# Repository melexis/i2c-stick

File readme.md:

# Melexis i2c-stick

Current version: V1.6.0

The web interface here:  
https://www.melexis.com/i2c-stick/

The i2c-stick:  
[web_interface/i2c-stick.md](web_interface/i2c-stick.md)

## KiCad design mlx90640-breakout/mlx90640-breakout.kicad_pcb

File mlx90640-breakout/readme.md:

# MLX90640-41 Breakout

## The sensor

Breakout PBC for MLX90640 & MLX90641:  
https://melexis.com/mlx90640  
https://melexis.com/mlx90641

Order codes for the sensor:

### MLX90640:  

32x24 pixel thermal camera

- MLX90640ESF-BAB-000-SP: Small FoV (55x35)
- MLX90640ESF-BAA-000-SP: Wide FoV (110x75)

### MLX90641:

16x12 pixel thermal camera

- MLX90641ESF-BCA-000-SP: Small FoV (55x35)
- MLX90641ESF-BCB-000-SP: Wide FoV (110x75)

Or contact our sales team at: https://www.melexis.com/en/contact/sales-contact

Where to buy? https://www.melexis.com/en/contact/distributors

## Get started

This board works together with any 3.3V I2C master.  
Have a look at our `I2C STICK` for evaluation pursposes.  
The board uses the QWIIC connector system for I2C & Supply.

QWIIC: https://www.sparkfun.com/qwiic

## The board

### Schema

### Layout

### 3D View

### 3D Model

[mlx90640-breakout.step](output/mlx90640-breakout.step)  

### Images

todo

### Optional socket:

Mill-Max Manufacturing Corp. - 917-43-208-41-005000  
  
https://www.digikey.com/en/products/detail/mill-max-manufacturing-corp/917-43-208-41-005000/1212173   
Note: 4 pins would have to be cut in order to fit the foot print.

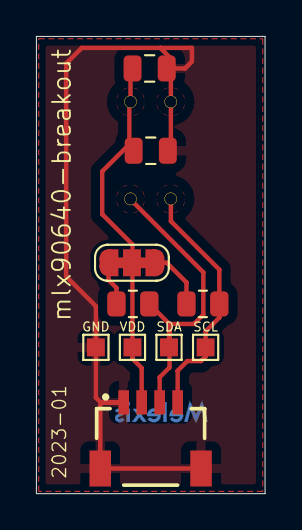
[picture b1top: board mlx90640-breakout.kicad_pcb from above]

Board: 2 copper layers, 12.7 x 25.4 mm, 11 parts (1 on the bottom side), 6 nets.

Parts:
C1: 100n; C_0805_2012Metric
C2: 10u; C_0805_2012Metric
GND: TestPoint; TestPoint_Pad_1.0x1.0mm
J1: Conn_01x04_Male; QWIIC_STEMMA_QT
JP1: SolderJumper_3_Bridged123; SolderJumper-3_P1.3mm_Bridged12_RoundedPad1.0x1.5mm_NumberL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
R1, R2: 4K7; R_0805_2012Metric
SCL: TestPoint; TestPoint_Pad_1.0x1.0mm
SDA: TestPoint; TestPoint_Pad_1.0x1.0mm
U1: MLX90640; mlx90640_41
VDD: TestPoint; TestPoint_Pad_1.0x1.0mm

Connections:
/GND: C1.2, C2.2, GND.1, J1.1, J1.NC1, J1.NC2, U1.3 (GND)
/SCL: J1.4, R1.2, SCL.1, U1.4 (SCL)
/SDA: J1.3, R2.2, SDA.1, U1.1 (SDA)
/VDD: C1.1, C2.1, J1.2, JP1.2 (C), U1.2 (VDD), VDD.1
unnamed: JP1.1 (A), R2.1
unnamed: JP1.3 (B), R1.1

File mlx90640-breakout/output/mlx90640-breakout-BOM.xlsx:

Item | Qty | Reference(s) | Value | LibPart | Footprint | Datasheet
1 | 1 | C1 | 100n | pspice:C | Capacitor_SMD:C_0805_2012Metric | ~
2 | 1 | C2 | 10u | pspice:C | Capacitor_SMD:C_0805_2012Metric | ~
3 | 1 | J1 | Conn_01x04_Male | Connector:Conn_01x04_Male | melexis-temperature:QWIIC_STEMMA_QT | https://www.sparkfun.com/products/14417
5 | 2 | R1, R2 | 4K7 | Device:R | Resistor_SMD:R_0805_2012Metric | ~
7 | 1 | U1 | MLX90640 | melexis-temperature:MLX90640 | melexis-temperature:mlx90640_41 | https://melexis.com/mlx90640
 |  |  | Alt #1 | MLX90640ESF-BAA-000-TU | 32x24 pixel, wide field of view
 |  |  | Alt #2 | MLX90640ESF-BAB-000-TU | 32x24 pixel, small field of view
 |  |  | Alt #3 | MLX90641ESF-BCA-000-TU | 16x12 pixel, wide field of view
 |  |  | Alt #4 | MLX90641ESF-BCB-000-TU | 16x12 pixel, small field of view

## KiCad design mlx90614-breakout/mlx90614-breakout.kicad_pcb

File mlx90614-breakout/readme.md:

# MLX90614 Breakout

## The sensor

Breakout PBC for MLX90614:  
https://melexis.com/mlx90614

Order codes for the sensor:

### Standard accuracy:  

- MLX90614ESF-BAA-000-SP: 90 Deg FoV
- MLX90614ESF-BCC-000-SP: 35 Deg FoV
- MLX90614ESF-BCF-000-SP: 10 Deg FoV
- MLX90614ESF-BCI-000-SP:  5 Deg FoV

### Medical Accuracy:

- MLX90614ESF-DCC-000-SP: 35 Deg FoV
- MLX90614ESF-DCI-000-SP:  5 Deg FoV

Contact our sales team at: https://www.melexis.com/en/contact/sales-contact

Where to buy? https://www.melexis.com/en/contact/distributors

## Get started

This board works together with any 3.3V I2C master.  
Have a look at our `I2C STICK` for evaluation pursposes.  
The board uses the QWIIC connector system for I2C & Supply.

QWIIC: https://www.sparkfun.com/qwiic

## The board

### Schema

### Layout

### 3D View

### 3D Model

[mlx90614-breakout.step](output/mlx90614-breakout.step)  

### Images

todo

### Optional socket:

Mill-Max Manufacturing Corp. - 917-43-104-41-005000  
  
https://www.digikey.com/en/products/detail/mill-max-manufacturing-corp/917-43-104-41-005000/1212171

### Optional spacer:

PCB to sensor spacer:  
https://www.digikey.com/en/products/detail/bivar-inc/514-070/3096249  
https://www.digikey.com/en/products/detail/assmann-wsw-components/V4555/3511514

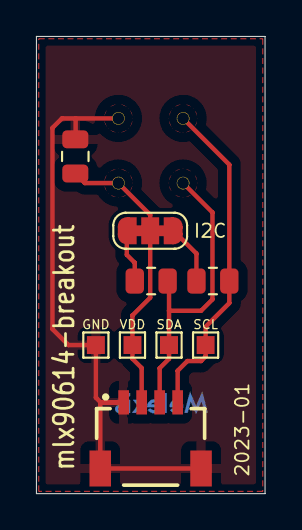
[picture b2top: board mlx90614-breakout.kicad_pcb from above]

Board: 2 copper layers, 12.7 x 25.4 mm, 10 parts (1 on the bottom side), 6 nets.

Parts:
C1: 100n; C_0805_2012Metric
GND: TestPoint; TestPoint_Pad_1.0x1.0mm
I2C: SolderJumper_3_Bridged123; SolderJumper-3_P1.3mm_Bridged12_RoundedPad1.0x1.5mm_NumberL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
J1: Conn_01x04_Male; QWIIC_STEMMA_QT
R1, R2: 4K7; R_0805_2012Metric
SCL: TestPoint; TestPoint_Pad_1.0x1.0mm
SDA: TestPoint; TestPoint_Pad_1.0x1.0mm
U1: MLX90614; mlx90614
VDD: TestPoint; TestPoint_Pad_1.0x1.0mm

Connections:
/GND: C1.2, GND.1, J1.1, J1.NC1, J1.NC2, U1.4 (VSS)
/SCL: J1.4, R1.2, SCL.1, U1.1 (SCL/VZ)
/SDA: J1.3, R2.2, SDA.1, U1.2 (SDA/PWM)
/VDD: C1.1, I2C.2 (C), J1.2, U1.3 (VDD), VDD.1
unnamed: I2C.1 (A), R2.1
unnamed: I2C.3 (B), R1.1

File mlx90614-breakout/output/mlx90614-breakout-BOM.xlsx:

Item | Qty | Reference(s) | Value | LibPart | Footprint | Datasheet | MANUFACTURER
1 | 1 | C1 | 100n | 90632_speculum_flex-rescue:C-pspice | Capacitor_SMD:C_0805_2012Metric
2 | 1 | J1 | Conn_01x04_Male | Connector:Conn_01x04_Male | melexis-temperature:QWIIC_STEMMA_QT | ~ | https://www.sparkfun.com/products/14417
4 | 2 | R1, R2 | 4K7 | Device:R | Resistor_SMD:R_0805_2012Metric | ~
6 | 1 | U1 | MLX90614 | melexis-temperature:MLX90614 | melexis-temperature:mlx90614 | https://melexis.com/mlx90614 | Melexis
 |  |  | Alt #1 | MLX90614ESF-DAA-000-TU | 3V, Medical accuracy, FoV 90, up to 180DegC
 |  |  | Alt #2 | MLX90614ESF-DCC-000-TU | 3V, Medical accuracy, FoV 35, up to 180DegC
 |  |  | Alt #3 | MLX90614ESF-DCI-000-TU | 3V, Medical accuracy, FoV 5, up to 180DegC
 |  |  | Alt #4 | MLX90614ESF-BAA-000-TU | 3V, Standard accuracy, FoV 90, up to 380DegC
 |  |  | Alt #5 | MLX90614ESF-BCC-000-TU | 3V, Standard accuracy, FoV 35, up to 380DegC
 |  |  | Alt #6 | MLX90614ESF-BCI-000-TU | 3V, Standard accuracy, FoV 5, up to 380DegC
 |  | U1-Spacer | optional #1 | white, small spacer |  |  | https://www.digikey.com/en/products/detail/bivar-inc/514-070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
 |  |  | optional #2 | red, larger spacer |  |  | https://www.digikey.com/en/products/detail/assmann-wsw-compo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

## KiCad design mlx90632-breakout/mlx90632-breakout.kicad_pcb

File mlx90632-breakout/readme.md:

# MLX90632 Breakout

## The sensor

Breakout PBC for MLX90632:  
https://melexis.com/mlx90632

Order codes for the sensor:

### Standard accuracy:  

- MLX90632SLD-BCB-000-RE: VDD=3.3V & 3.3V I2C levels

### Medical Accuracy:

- MLX90632SLD-DCB-000-RE: VDD=3.3V & 3.3V I2C levels
- MLX90632SLD-DCB-100-RE: VDD=3.3V & 1.8V I2C levels

Or contact our sales team at: https://www.melexis.com/en/contact/sales-contact

Where to buy? https://www.melexis.com/en/contact/distributors

## Get started

This board works together with any 3.3V I2C master.  
Have a look at our `I2C STICK` for evaluation pursposes.  
The board uses the QWIIC connector system for I2C & Supply.

QWIIC: https://www.sparkfun.com/qwiic

## The board

### Schema

### Layout

### 3D View

### 3D Model

[mlx90632-breakout.step](output/mlx90632-breakout.step)  

### Images

todo

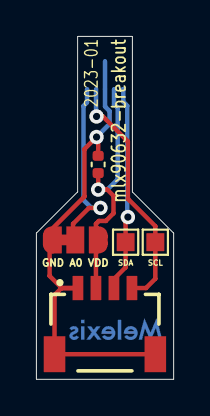
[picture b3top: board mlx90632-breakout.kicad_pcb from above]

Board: 2 copper layers, 7.6 x 19.0 mm, 6 parts (1 on the bottom side), 5 nets.

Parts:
C1: 10n; C_0402_1005Metric
GND A0 VDD: Jumper_3_Bridged12; SolderJumper-3_P1.3mm_Bridged12_RoundedPad1.0x1.5mm
J1: Conn_01x04_Male; QWIIC_STEMMA_QT
SCL: TestPoint; TestPoint_Pad_1.0x1.0mm
SDA: TestPoint; TestPoint_Pad_1.0x1.0mm
U1: MLX90632SLD-BCB-000-SP; MLX90632-no-via-large

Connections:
/GND: C1.2, GND A0 VDD.1 (A), J1.1, U1.3 (GND), U1.6 (EP)
/SCL: J1.4, SCL.1, U1.4 (SCL)
/SDA: J1.3, SDA.1, U1.1 (SDA)
/VDD: C1.1, GND A0 VDD.3 (B), J1.2, U1.2 (VDD)
unnamed: GND A0 VDD.2 (C), U1.5 (ADDR)

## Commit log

2023-03-03 initial version
2023-05-19 * bugfix: scan/ls cmd to list also slaves with unknown driver * add: pwm command * bugfix: MLX90632 issue unlock key prior EEPROM write * V1.3.0 candidate
2023-05-19 Initial commit for python package
2023-05-19 workflow #1
2023-05-19 workflow #2
2023-05-19 workflow #3
2023-05-19 workflow #4
2023-05-19 workflow #5
2023-05-19 workflow #7
2023-05-19 workflow #8
2023-05-19 workflow #9
2023-05-19 workflow #10
2023-05-19 workflow #11
2023-05-23 patch "fv" command end of line in return + update doc + add several commands to the I2CStick class
2023-05-24 update doc + python: adding commands to I2CStick class
2023-05-24 firmware: streamline value(description) format and command in response
2023-05-24 re-order the sequence of functions to match the doc/firmware
2023-05-24 python: add ch function
2023-05-24 fix: use decimal notation in cs command
2023-05-24 python add cs command
2023-05-30 * FW: add timestamp on raw command * FW: 90632 add MEAS_SELECT/COUNT configuration * PY: add cs_write command
2023-05-30 PY: patch version
2023-05-30 * PY: singed raw data
2023-05-31 * FW: Fix extern C compilation issue
2023-05-31 * FW: 90632 remove MEAS_COUNT config * FW: 90632 raw emit only last updated values * PY: update readme
2023-10-04 add txt file support + bump bincopy version to 18
2023-10-04 update config file
2023-10-04 fix minor issues
2023-10-11 adding automation tools + discover 90614 which are in PWM mode during an I2C-scan command
2023-10-20 fixed bugs
2023-10-20 empty file
2023-10-20 work in progress
2023-10-21 mlx90621 adding to the list; work in progress
2023-10-27 updating dodo file for other platforms + enable lib install when needed
2023-11-01 add todo; remove show cmd for dynamic commands
2023-11-01 reformat with pycharm
2023-11-01 allow check SA available from generic i2c command, let gernetic i2c command fail when amount of received bytes is not matching
2023-11-01 commit generated dispatcher; now each fresh doit compile will re-generated the dispatcher file based on context.yaml
2023-11-01 adding slave configuration to mlx90621
2023-11-02 add doc in python module + add 90621:sn/mw/mr commands
2023-11-03 update CH command format
2023-11-03 add doc + implement ch_write
2023-11-03 add modal pop up box for displaying errors to the users.
2023-11-04 typo
2023-11-04 removing enable chart checkbox
2023-11-04 more typos
2023-11-04 add info on spatial chart for MLX90640-41 only
2023-11-07 adding doit to generate the website
2023-11-07 first version of doit
2023-11-07 fix html errors round #1
2023-11-07 fix html errors round #2
2023-11-07 fix html errors round #3
2023-11-07 prep for bumpver; a single version for web/firmware/python
2023-11-07 bump version to 1.3.6 (from 1.3.5)
2023-11-07 bump version to 1.3.7 (from 1.3.6)
2023-11-08 adding install of nodejs
2023-11-08 adding install of nodejs packages and pandoc
2023-11-08 doit clean + add task dependencies
2023-11-08 fix naming convention + set node path correctly
2023-11-08 adding dist task
2023-11-09 update git workflow attempt #1
2023-11-09 update git workflow attempt #2
2023-11-09 update git workflow attempt #3
2023-11-09 update git workflow attempt #4
2023-11-09 update git workflow attempt #5
2023-11-09 update git workflow attempt #6
2023-11-09 update git workflow attempt #7
2023-11-09 update git workflow attempt #8
2023-11-09 update git workflow attempt #9
2023-11-09 update git workflow attempt #10
2023-11-09 update git workflow attempt #11
2023-11-09 update git workflow attempt #12
2023-11-09 update git workflow attempt #13
2023-11-09 update git workflow attempt #14
2023-11-09 update git workflow attempt #15
2023-11-09 update git workflow attempt #16
2023-11-09 update git workflow attempt #17
2023-11-09 update git workflow attempt #18
2023-11-09 update git workflow attempt #19
2023-11-09 update git workflow attempt #20
2023-11-09 update git workflow attempt #21
2023-11-09 cleanup + adding USB VID/PID list in javascript for pre-selecting USB I2C-sticks
2023-11-09 add MLX90621 to spatial viewer
2023-11-15 fixing I2C direct read functionality
2023-11-15 adding ESP32-C6
2023-11-16 generic extra_flags
2023-11-16 remove compile warnings
2023-11-16 remove mlx90621
2023-11-16 adding driver yaml files + fix compile warnings
2023-11-16 missing file
2023-11-16 fix file_dep
2023-11-16 adding debug
2023-11-16 remove debug
2023-11-17 reorganize .gitignore for plugin framework
2023-11-17 adding arduino plugins + update add-driver templating
2023-11-17 adding artifacts to the release tag
2023-11-17 with tags
2023-11-17 with write permission
2023-11-17 bump version to 1.3.8 (from 1.3.7)
2023-11-17 bump version to 1.3.9 (from 1.3.8)
2023-11-18 add disable to boards in context config file + add empty plugins directory
2023-11-18 bump version to 1.3.10 (from 1.3.9)
2023-11-18 add same disable rules for web-interace as for arduino
2023-11-18 bump version to 1.3.11 (from 1.3.10)
2023-11-18 add disable flag support for web-interface
2023-11-18 bump version to 1.3.12 (from 1.3.11)
2023-11-18 remove no longer needed files
2023-11-18 bump version to 1.3.13 (from 1.3.12)
2023-11-20 fix hamburger function
2024-02-02 update typos + add pin command + add sent button
2024-02-02 disable teensy
2024-02-02 bump version to 1.3.14 (from 1.3.13)
2024-02-02 bump version to 1.3.15 (from 1.3.14)
2024-02-02 bump version to 1.3.16 (from 1.3.15)
2024-02-02 fixed typo
2024-02-02 bump version to 1.4.0 (from 1.3.16)
2024-09-06 adding MLX90394 + app framework
2024-09-06 bump version to 1.5.0 (from 1.4.0)
2024-10-30 adding step by step documentation on how to update the refresh rate for the MLX90632 standard mode
2024-10-30 add intro and fixed minor flaws
2024-10-30 adding I2C command doc to update the refresh rate
2024-10-30 line spacing
2025-01-20 adding user interface for 90642 + joystick support
2025-01-20 bump version to 1.5.1 (from 1.5.0)
2025-01-20 temporary disable the CAL function
2025-01-20 bump version to 1.5.2 (from 1.5.1)
